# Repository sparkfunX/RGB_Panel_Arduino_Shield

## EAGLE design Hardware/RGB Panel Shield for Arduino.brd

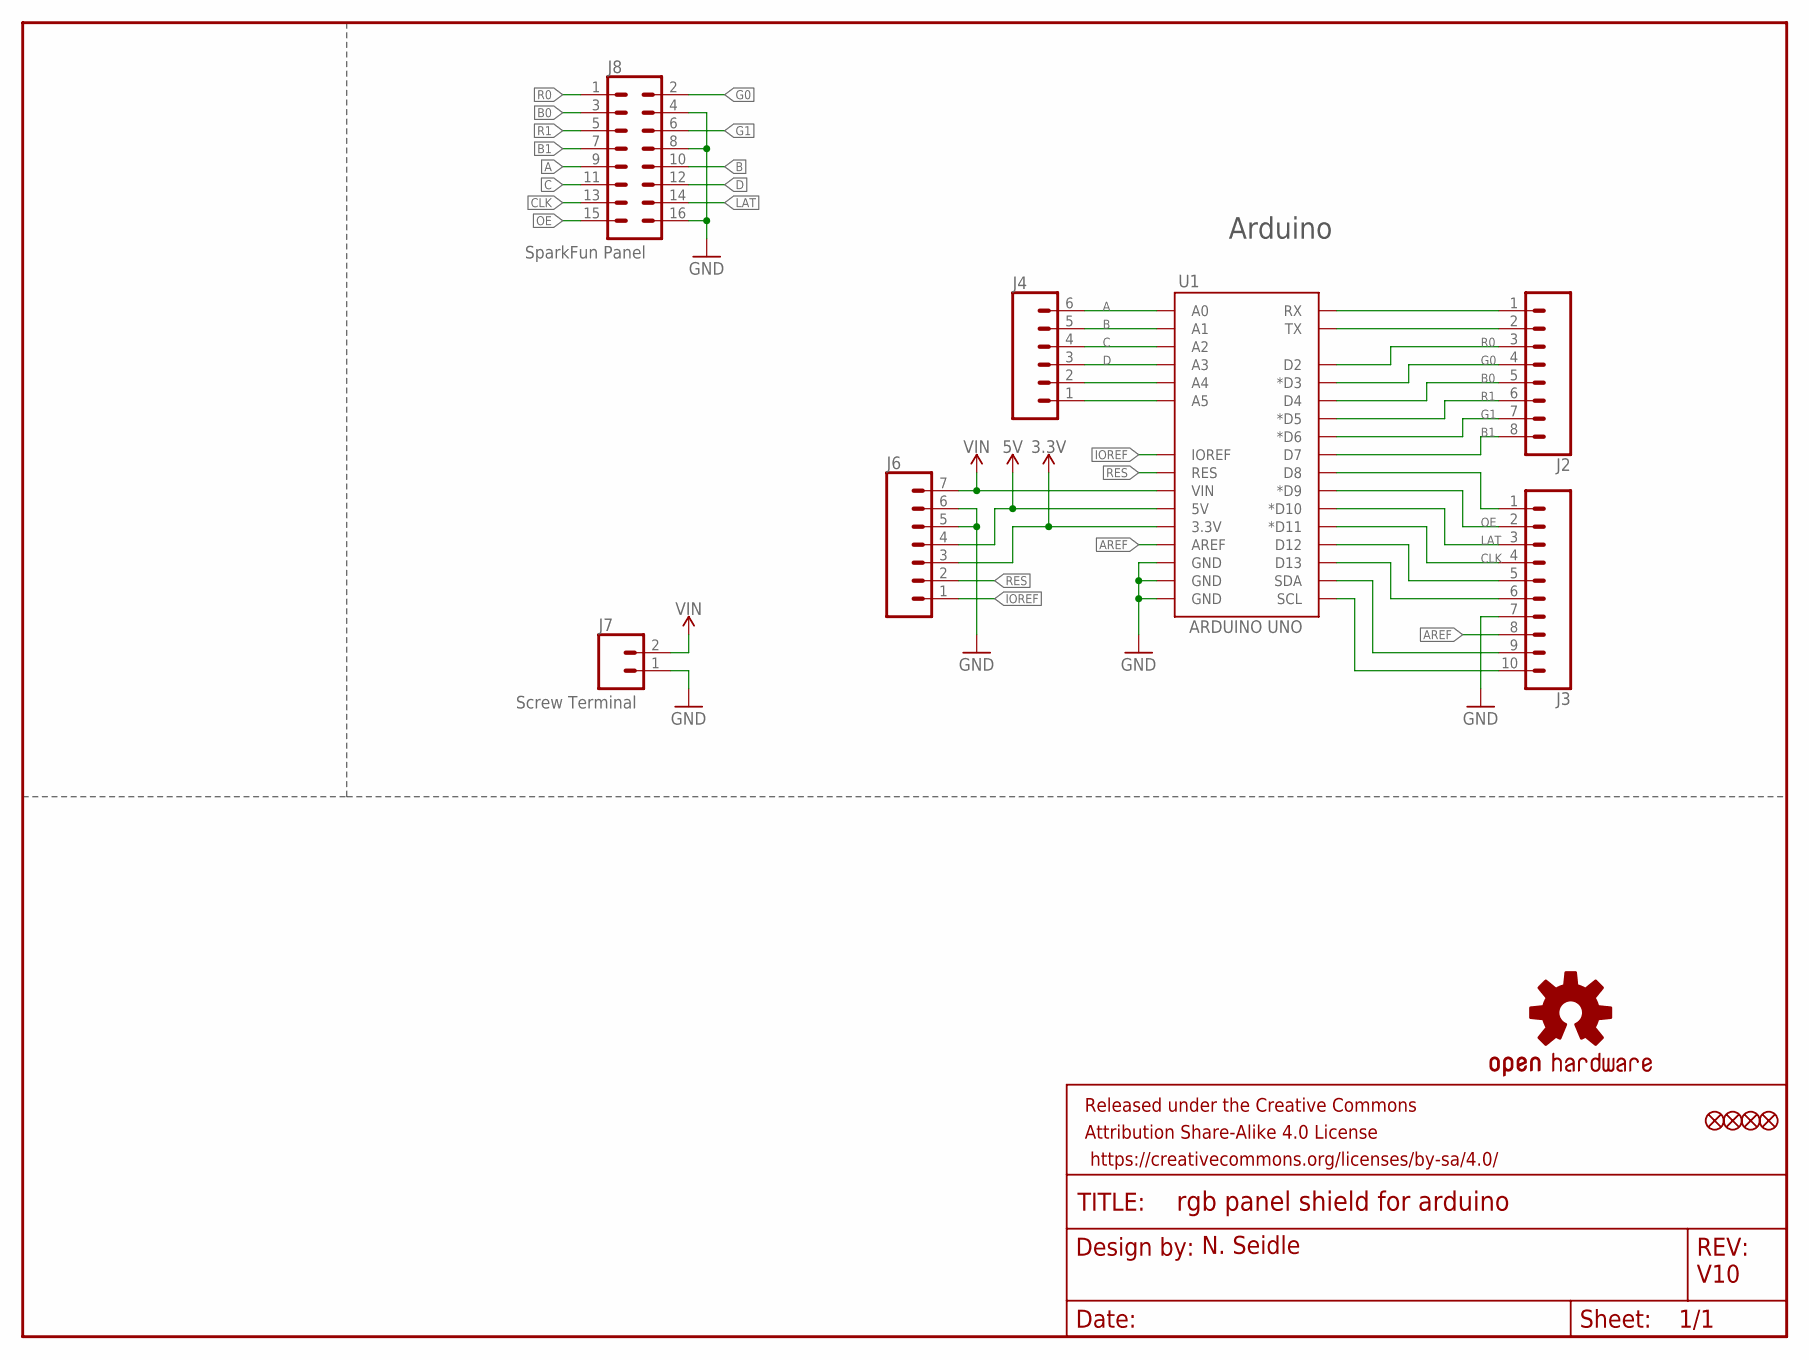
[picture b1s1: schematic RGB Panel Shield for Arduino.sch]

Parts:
FD1, FD2, FD3, FD4: FIDUCIAL1X2; FIDUCIAL-1X2
FRAME1: FRAME-LETTER; CREATIVE_COMMONS
J2: CONN_08NO_SILK_FEMALE_PTH; 1X08_NO_SILK
J3: CONN_10NO_SILK_PTH_FEMALE; 1X10_NO_SILK
J4: CONN_06NO_SILK_FEMALE_PTH; 1X06_NO_SILK
J6: CONN_07NO_SILK; 1X07_NO_SILK
J7: Screw Terminal; SCREWTERMINAL-5MM-2
J8: SparkFun Panel; 2X8-SHROUDED_LOCK
LOGO1: OSHW-LOGOMINI; OSHW-LOGO-MINI
U1: ARDUINO UNO; UNO_R3_SHIELD_NOLABELS

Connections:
3.3V: J6.3, U1.3.3V
5V: J6.4, U1.5V
A: J4.6, J8.9, U1.A0
A4: J4.2, U1.A4
A5: J4.1, U1.A5
AREF: J3.8, U1.AREF
B: J4.5, J8.10, U1.A1
B0: J2.5, J8.3, U1.D4
B1: J2.8, J8.7, U1.D7
C: J4.4, J8.11, U1.A2
CLK: J3.4, J8.13, U1.D11 (*D11)
D: J4.3, J8.12, U1.A3
D8: J3.1, U1.D8
D12: J3.5, U1.D12
D13: J3.6, U1.D13
G0: J2.4, J8.2, U1.D3 (*D3)
G1: J2.7, J8.6, U1.D6 (*D6)
GND: J3.7, J6.5, J6.6, J7.1, J8.4, J8.8, J8.16, U1.GND@0 (GND), U1.GND@1 (GND), U1.GND@2 (GND)
IOREF: J6.1, U1.IOREF
LAT: J3.3, J8.14, U1.D10 (*D10)
OE: J3.2, J8.15, U1.D9 (*D9)
R0: J2.3, J8.1, U1.D2
R1: J2.6, J8.5, U1.D5 (*D5)
RES: J6.2, U1.RES
RX: J2.1, U1.RX
SCL1: J3.10, U1.SCL
SDA1: J3.9, U1.SDA
TX: J2.2, U1.TX
VIN: J6.7, J7.2, U1.VIN

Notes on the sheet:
N. Seidle
Arduino
V10

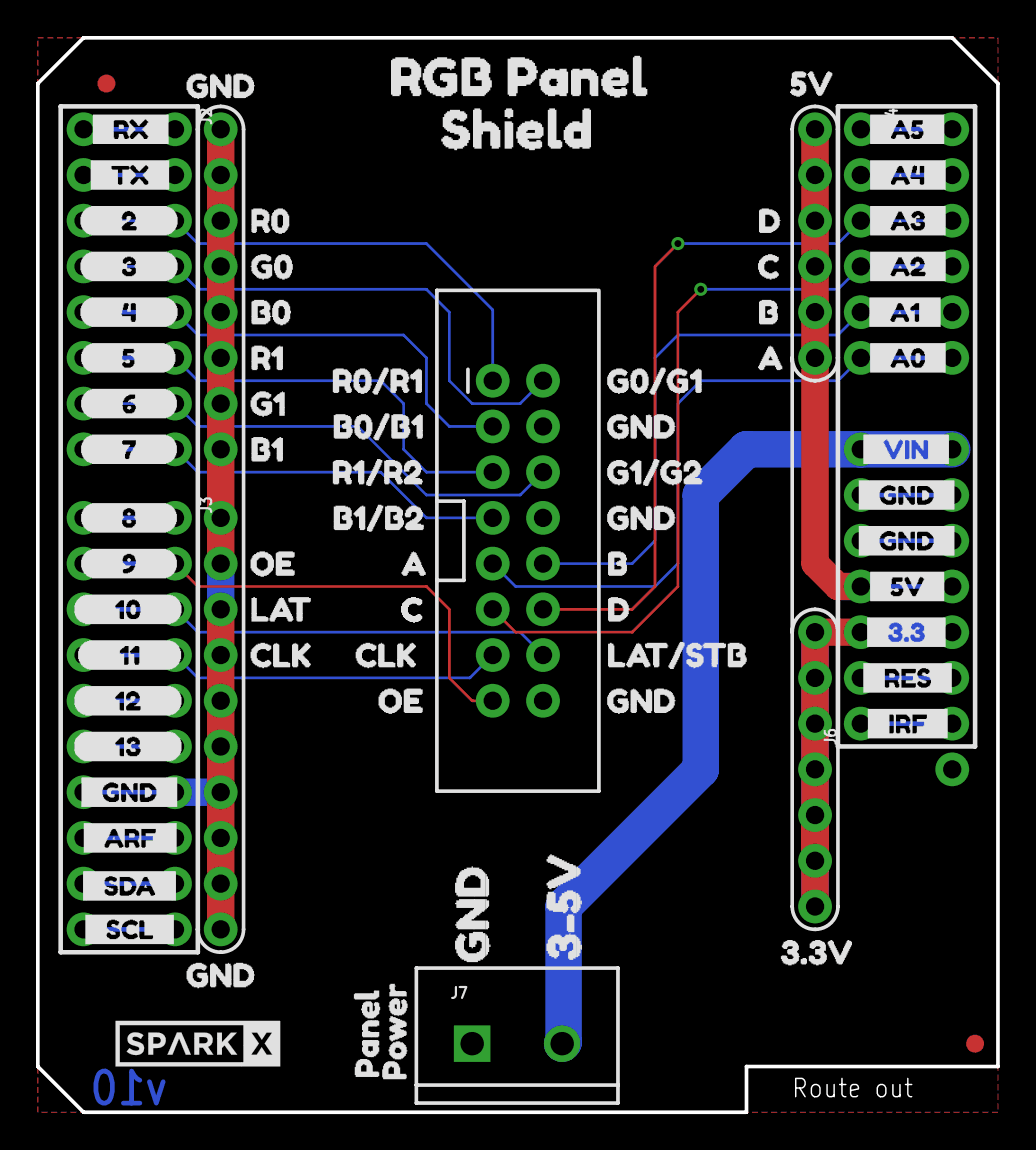
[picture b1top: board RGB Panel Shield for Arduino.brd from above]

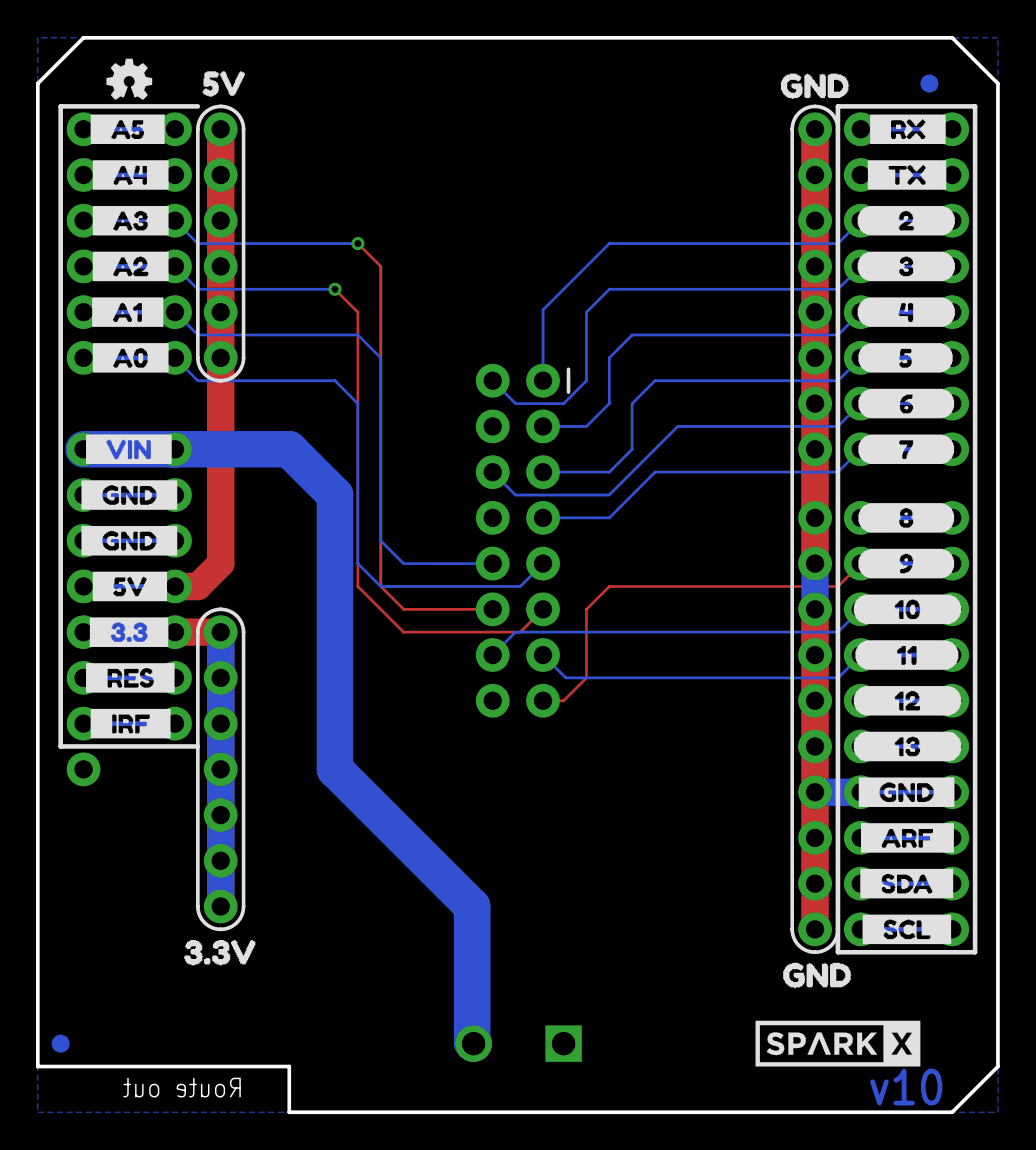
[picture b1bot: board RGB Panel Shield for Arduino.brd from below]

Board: 2 copper layers, 53.3 x 59.7 mm, 121 parts (39 on the bottom side), 29 nets.

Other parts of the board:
U$1, U$34: D42
U$2, U$128: SPARKX-MEDIUM
U$3, U$32, U$113: C37
U$4, U$38: GND48
U$5: 3#5V3
U$6, U$79: ____2____1
U$7, U$80: ____3____3
U$8, U$81: ____4____4
U$9, U$82: ____5____5
U$10, U$83: ____6____6
U$11: GND2
U$12, U$84: ____7____7
U$13, U$85: ____8____8
U$14, U$86: ____9____9
U$15, U$87: ____10____10
U$16: PANEL0
U$17, U$88: ____11____11
U$18, U$89: ____12____12
U$19: POWER1
U$20, U$90: ____13____13
U$21, U$22, U$37, U$108, U$109: GND40
U$23: RGB_PANEL2
U$24, U$73: __RX__0
U$25, U$110: 3#3V46
U$26, U$107: 5V47
U$27, U$45: __3#3__27
U$28, U$115: A36
U$29: B0#B132
U$30: B1#B235
U$31, U$114: B43
U$33, U$121: CLK38
U$35: G0#G145
U$36: G1#G244
U$39: LAT#STB41
U$40, U$122: OE39
U$41: R0#R131
U$42: R1#R234
U$43, U$48: __5V__26
U$44, U$62: __A0__23
U$46, U$63: __A1__22
U$47, U$64: __A2__21
U$49, U$65: __A3__20
U$50, U$66: __A4__19
U$51, U$72: __A5__18
U$52, U$74: __ARF__15
U$53, U$75: __GND__14
U$54, U$55, U$67, U$68: __GND__25
U$56, U$71: __IRF__29
U$57, U$69: __RES__28
U$58, U$76: __SCL__17
U$59, U$77: __SDA__16
U$60, U$78: __TX__0
U$61, U$70: __VIN__24
U$112: B15
U$116: B03
U$117: G01
U$118: G14
U$119: R00
U$120: R12
U$123: LAT0
U$124: SHIELD0

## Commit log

2018-05-22 Readme fix

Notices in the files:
parts and their libraries:
SparkFun-Boards: Licensing: CC v3.0 Share-Alike You are welcome to use this library for commercial purposes.
SparkFun-Aesthetics: Released under the Creative Commons Attribution Share-Alike 4.0 License
SparkFun-Aesthetics: https://creativecommons.org/licenses/by-sa/4.0
